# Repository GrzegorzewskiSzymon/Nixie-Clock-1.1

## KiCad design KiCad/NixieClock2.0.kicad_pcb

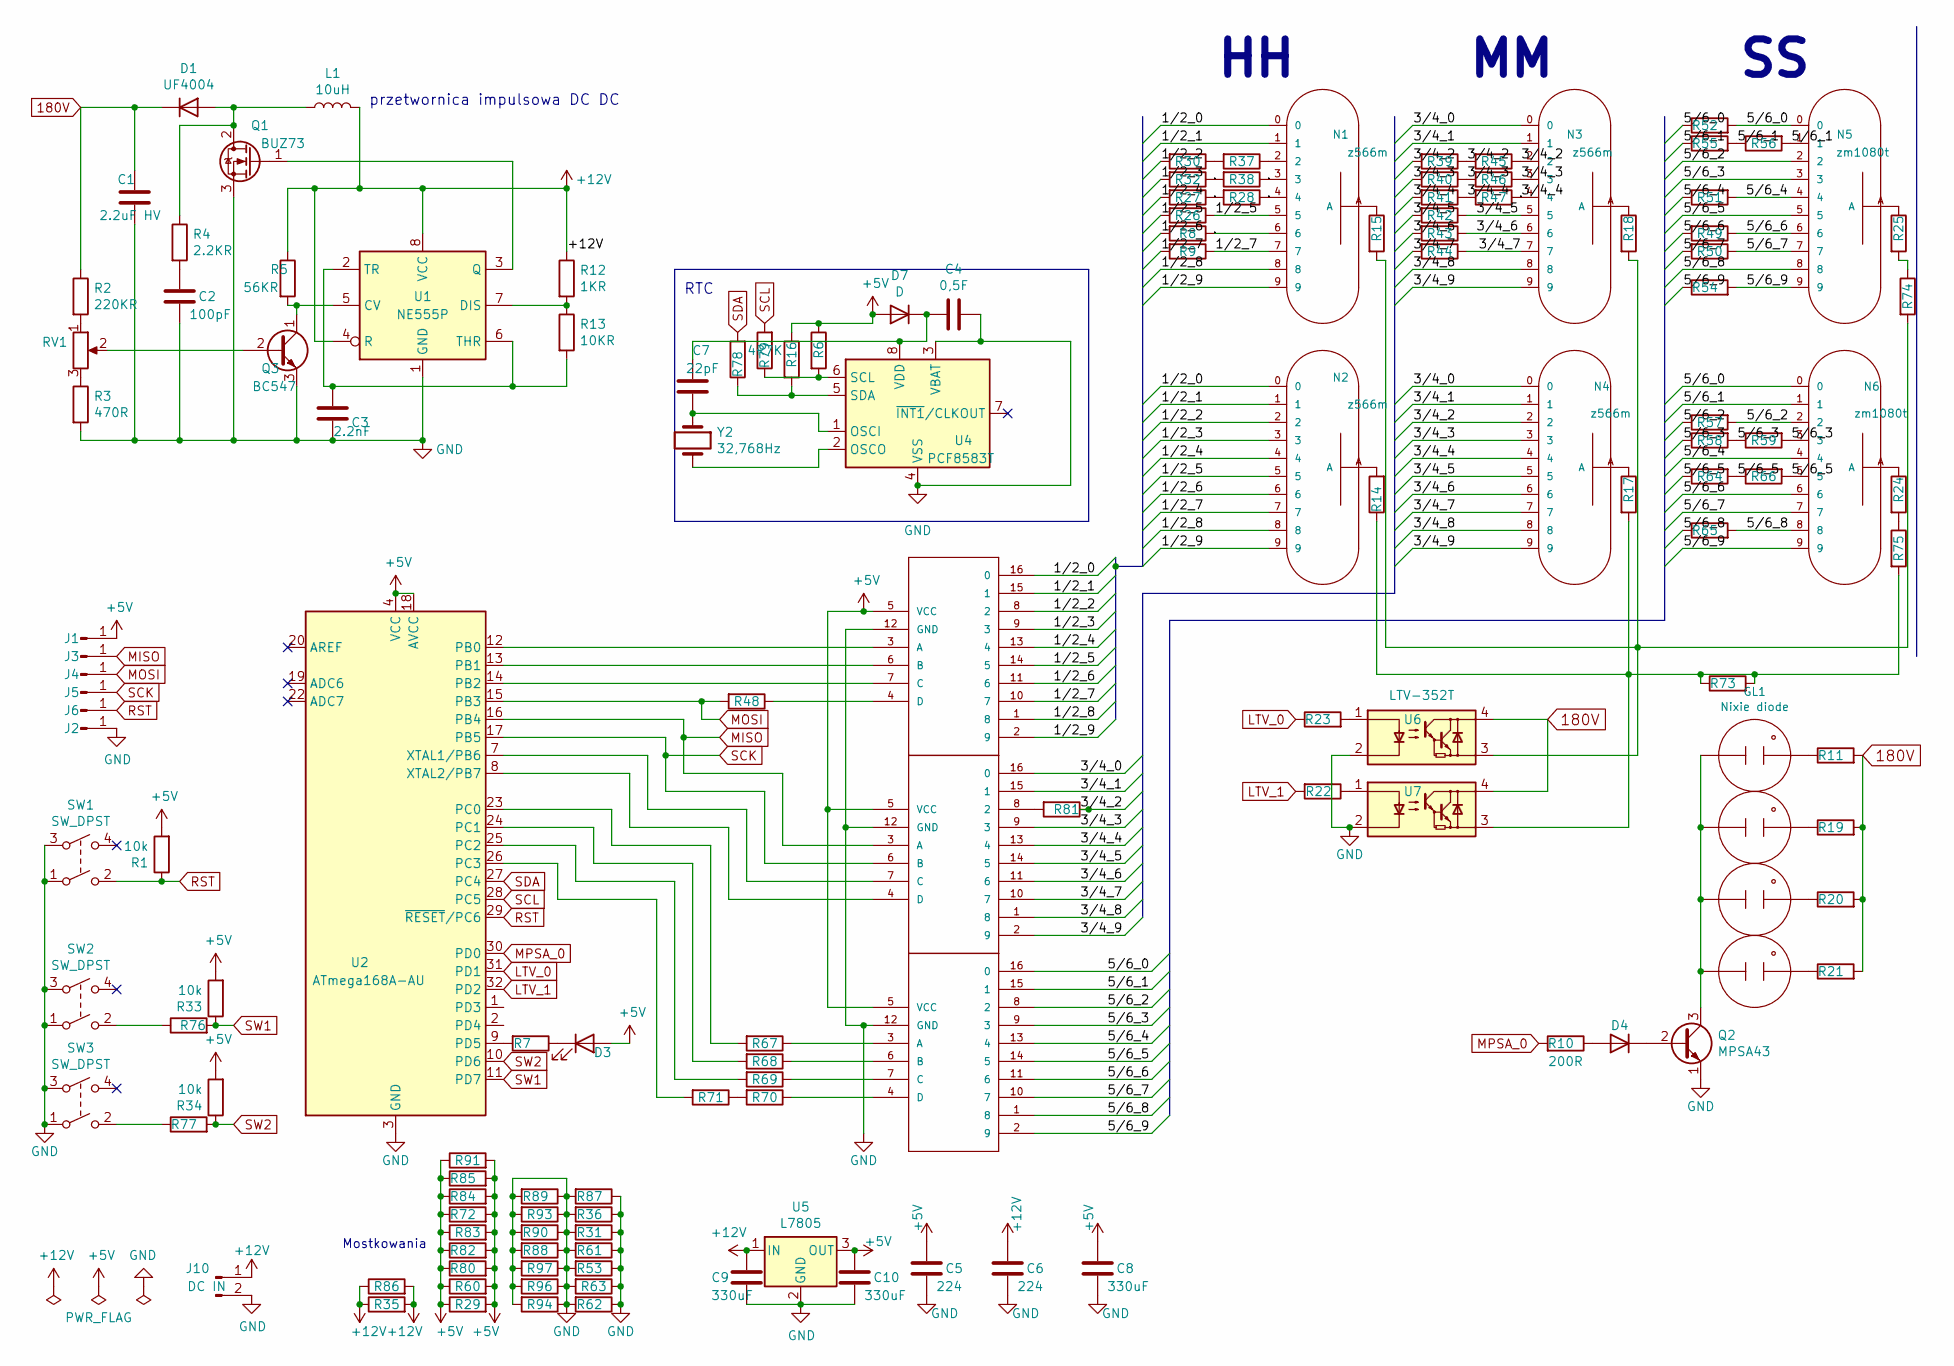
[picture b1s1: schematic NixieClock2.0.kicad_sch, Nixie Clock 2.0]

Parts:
C1: 2.2uF HV; CP_Radial_D8.0mm_P3.80mm
C2: 100pF; C_Disc_D5.0mm_W2.5mm_P5.00mm
C3: 2.2nF; C_Disc_D3.0mm_W2.0mm_P2.50mm
C4: 0,5F; CP_Radial_D6.3mm_P2.50mm
C5, C6: 224; C_Disc_D5.0mm_W2.5mm_P5.00mm
C7: 22pF; C_Disc_D3.0mm_W2.0mm_P2.50mm
C8, C9, C10: 330uF; CP_Radial_D5.0mm_P2.50mm
D1, D4: UF4004; D_DO-35_SOD27_P7.62mm_Horizontal
D3: LED; LED_1206_3216Metric_Pad1.42x1.75mm_HandSolder
D7: D; D_DO-34_SOD68_P7.62mm_Horizontal
GL1, GL2, GL3, GL4: Nixie diode; PinHeader_1x02_P2.54mm_Vertical
J1, J2, J3, J4, J5, J6: Conn_01x01_Male; PinHeader_1x01_P2.54mm_Vertical
J10: DC IN; BarrelJack_CUI_PJ-102AH_Horizontal
L1: 10uH; L_Axial_L6.6mm_D2.7mm_P2.54mm_Vertical_Vishay_IM-2
M1, M2, M3: 74141SOIC16; DIP-16_W7.62mm_LongPads
N1, N2, N3, N4: z566m; z566M
N5, N6: zm1080t; zm1080T
Q1: BUZ73; TO-220-3_Vertical
Q2: MPSA43; TO-92_Inline
Q3: BC547; TO-92_Inline
R1, R33, R34: 10k; R_1206_3216Metric_Pad1.30x1.75mm_HandSolder
R2: 220KR; R_1206_3216Metric_Pad1.30x1.75mm_HandSolder
R3: 470R; R_Axial_DIN0207_L6.3mm_D2.5mm_P7.62mm_Horizontal
R4: 2.2KR; R_1206_3216Metric_Pad1.30x1.75mm_HandSolder
R5: 56KR; R_1206_3216Metric_Pad1.30x1.75mm_HandSolder
R6, R16: 4R7K; R_1206_3216Metric_Pad1.30x1.75mm_HandSolder
R7: 340R; R_Axial_DIN0207_L6.3mm_D2.5mm_P7.62mm_Horizontal
R8, R9, R26, R27, R28, R29, R30, R32, R35, R37, R38, R39, R40, R41, R42, R43, R44, R45, R46, R47, R48, R49, R50, R51, R56, R57, R58, R59, R60, R63, R64, R66, R67, R68, R69, R70, R71, R74, R75, R83, R86, R91, R93, R94, R96, R97: 0R; R_1206_3216Metric_Pad1.30x1.75mm_HandSolder
R10: 200R; R_1206_3216Metric_Pad1.30x1.75mm_HandSolder
R11, R19, R20, R21: 470KR; R_1206_3216Metric_Pad1.30x1.75mm_HandSolder
R12: 1KR; R_1206_3216Metric_Pad1.30x1.75mm_HandSolder
R13: 10KR; R_1206_3216Metric_Pad1.30x1.75mm_HandSolder
R14, R15, R17, R18: 47KR; R_Axial_DIN0207_L6.3mm_D2.5mm_P7.62mm_Horizontal
R22, R23: 340R; R_1206_3216Metric_Pad1.30x1.75mm_HandSolder
R24, R25: 56KR; R_Axial_DIN0207_L6.3mm_D2.5mm_P7.62mm_Horizontal
R31, R36, R52, R53, R54, R55, R61, R62, R65, R72, R73, R76, R77, R78, R79, R80, R81, R82, R84, R85, R87, R88, R89, R90: 0R; R_Axial_DIN0207_L6.3mm_D2.5mm_P7.62mm_Horizontal
RV1: R_POT 1K; Potentiometer_ACP_CA9-H2,5_Horizontal
SW1: SW_DPST; SW_PUSH_6mm_H4.3mm
SW2, SW3: SW_DPST; SW_PUSH-12mm
U1: NE555P; DIP-8_W7.62mm
U2: ATmega168A-AU; TQFP-32_7x7mm_P0.8mm
U4: PCF8583T; SOIC-8_7.5x5.85mm_P1.27mm
U5: L7805; DPAK-3
U6, U7: LTV-352T; SO-4_4.4x3.6mm_P2.54mm
Y2: 32,768Hz; Crystal_DS15_D1.5mm_L5.0mm_Vertical

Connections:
180V: C1.1, D1.1 (K), R2.1, R11.2, R19.2, R20.2, R21.2, U6.4, U7.4
+5V: C5.1, C8.1, C10.1, D3.2 (A), D7.2 (A), J1.1, M1.5 (VCC), M2.5 (VCC), M3.5 (VCC), R1.2, R6.1, R16.1, R29.1, R29.2, R33.2, R34.2, R60.1, R60.2, R72.1, R72.2, R80.1, R80.2, R82.1, R82.2, R83.1, R83.2, R84.1, R84.2, R85.1, R85.2, R91.1, R91.2, U2.4 (VCC), U2.6 (VCC), U2.18 (AVCC), U5.3 (OUT)
+12V: C6.1, C9.1, J10.1, L1.2, R5.1, R12.1, R35.1, R35.2, R86.1, R86.2, U1.4 (R), U1.8 (VCC), U5.1 (IN)
/1/2_0: M1.16 (0), N1.0, N2.0
/1/2_1: M1.15 (1), N1.1, N2.1
/1/2_2: M1.8 (2), N2.2, R30.2
/1/2_3: M1.9 (3), N1.3, N2.3, R32.1, R32.2, R38.1, R38.2
/1/2_4: M1.13 (4), N1.4, N2.4, R27.1, R27.2, R28.1, R28.2
/1/2_5: M1.14 (5), N1.5, N2.5, R26.1, R26.2
/1/2_6: M1.11 (6), N1.6, N2.6, R8.1, R8.2
/1/2_7: M1.10 (7), N1.7, N2.7, R9.1, R9.2
/1/2_8: M1.1 (8), N1.8, N2.8
/1/2_9: M1.2 (9), N1.9, N2.9
/3/4_0: M2.16 (0), N3.0, N4.0
/3/4_1: M2.15 (1), N3.1, N4.1
/3/4_2: N3.2, N4.2, R39.1, R39.2, R45.1, R45.2, R81.1
/3/4_3: M2.9 (3), N3.3, N4.3, R40.1, R40.2, R46.1, R46.2
/3/4_4: M2.13 (4), N3.4, N4.4, R41.1, R41.2, R47.1, R47.2
/3/4_5: M2.14 (5), N3.5, N4.5, R42.1, R42.2
/3/4_6: M2.11 (6), N3.6, N4.6, R43.1, R43.2
/3/4_7: M2.10 (7), N3.7, N4.7, R44.1, R44.2
/3/4_8: M2.1 (8), N3.8, N4.8
/3/4_9: M2.2 (9), N3.9, N4.9
/5/6_0: M3.16 (0), N5.0, N6.0, R52.1, R52.2
/5/6_1: M3.15 (1), N5.1, N6.1, R55.1, R55.2, R56.1, R56.2
/5/6_2: M3.8 (2), N5.2, N6.2, R57.1, R57.2
/5/6_3: M3.9 (3), N5.3, N6.3, R58.1, R58.2, R59.1, R59.2
/5/6_4: M3.13 (4), N5.4, N6.4, R51.1, R51.2
/5/6_5: M3.14 (5), N5.5, N6.5, R64.1, R64.2, R66.1, R66.2
/5/6_6: M3.11 (6), N5.6, N6.6, R49.1, R49.2
/5/6_7: M3.10 (7), N5.7, N6.7, R50.1, R50.2
/5/6_8: M3.1 (8), N5.8, N6.8, R65.1, R65.2
/5/6_9: M3.2 (9), N5.9, N6.9, R54.1, R54.2
GND: C1.2, C2.2, C3.2, C4.2, C5.2, C6.2, C8.2, C9.2, C10.2, J2.1, J10.2, M1.12 (GND), M2.12 (GND), M3.12 (GND), Q1.3 (S), Q2.1 (E), Q3.3 (E), R3.2, R31.1, R31.2, R36.1, R36.2, R53.1, R53.2, R61.1, R61.2, R62.1, R62.2, R63.1, R63.2, R87.1, R87.2, R88.1, R88.2, R89.1, R89.2, R90.1, R90.2, R93.1, R93.2, R94.1, R94.2, R96.1, R96.2, R97.1, R97.2, SW1.1, SW1.3, SW2.1, SW2.3, SW3.1, SW3.3, U1.1 (GND), U2.3 (GND), U2.5 (GND), U2.21 (GND), U4.3 (VBAT), U4.4 (VSS), U5.2 (GND), U6.2, U7.2
LTV_0: R23.1, U2.31 (PD1)
LTV_1: R22.2, U2.32 (PD2)
MISO: J3.1, M2.3 (A), U2.16 (PB4)
MOSI: J4.1, R48.2, U2.15 (PB3)
MPSA_0: R10.2, U2.30 (PD0)
unnamed: C2.1, R4.2
unnamed: C3.1, R13.2, U1.2 (TR), U1.6 (THR)
unnamed: C4.1, C7.2, D7.1 (K), U4.8 (VDD)
unnamed: C7.1, U4.1 (OSCI), Y2.1
unnamed: D1.2 (A), L1.1, Q1.2 (D), R4.1
unnamed: D3.1 (K), R7.1
unnamed: D4.1 (K), Q2.2 (B)
unnamed: D4.2 (A), R10.1
unnamed: GL1.1 (A), GL2.1 (A), GL3.1 (A), GL4.1 (A), Q2.3 (C)
unnamed: GL1.2 (A1), R11.1
unnamed: GL2.2 (A1), R19.1
unnamed: GL3.2 (A1), R20.1
unnamed: GL4.2 (A1), R21.1
unnamed: M1.3 (A), U2.12 (PB0)
unnamed: M1.4 (D), R48.1
unnamed: M1.6 (B), U2.13 (PB1)
unnamed: M1.7 (C), U2.14 (PB2)
unnamed: M2.4 (D), U2.8 (XTAL2/PB7)
unnamed: M2.7 (C), U2.7 (XTAL1/PB6)
unnamed: M2.8 (2), R81.2
unnamed: M3.3 (A), R67.1
unnamed: M3.4 (D), R70.1
unnamed: M3.6 (B), R68.1
unnamed: M3.7 (C), R69.1
unnamed: N1.2, R37.1
unnamed: N1.A, R15.1
unnamed: N2.A, R14.2
unnamed: N3.A, R18.1
unnamed: N4.A, R17.1
unnamed: N5.A, R25.1
unnamed: N6.A, R24.1
unnamed: Q1.1 (G), U1.3 (Q)
unnamed: Q3.1 (C), R5.2, U1.5 (CV)
unnamed: Q3.2 (B), RV1.2
unnamed: R2.2, RV1.1
unnamed: R3.1, RV1.3
unnamed: R6.2, R79.1, U4.6 (SCL)
unnamed: R7.2, U2.9 (PD5)
unnamed: R12.2, R13.1, U1.7 (DIS)
unnamed: R14.1, R17.2, R73.1, R73.2, R75.2, U7.3
unnamed: R15.2, R18.2, R74.2, U6.3
unnamed: R16.2, R78.1, U4.5 (SDA)
unnamed: R22.1, U7.1
unnamed: R23.2, U6.1
unnamed: R24.2, R75.1
unnamed: R25.2, R74.1
unnamed: R30.1, R37.2
unnamed: R67.2, U2.23 (PC0)
unnamed: R68.2, U2.24 (PC1)
unnamed: R69.2, U2.25 (PC2)
unnamed: R70.2, R71.1
unnamed: R71.2, U2.26 (PC3)
unnamed: R76.1, SW2.2
unnamed: R77.1, SW3.2
unnamed: U4.2 (OSCO), Y2.2
RST: J6.1, R1.1, SW1.2, U2.29 (~RESET/PC6)
SCK: J5.1, M2.6 (B), U2.17 (PB5)
SCL: R79.2, U2.28 (PC5)
SDA: R78.2, U2.27 (PC4)
SW1: R33.1, R76.2, U2.11 (PD7)
SW2: R34.1, R77.2, U2.10 (PD6)

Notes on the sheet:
RTC
Mostkowania
przetwornica impulsowa DC DC

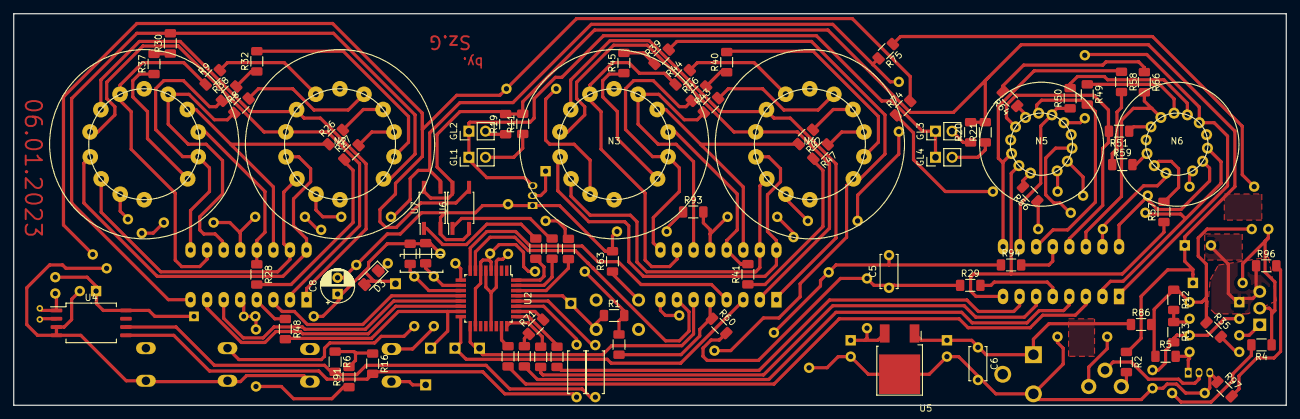
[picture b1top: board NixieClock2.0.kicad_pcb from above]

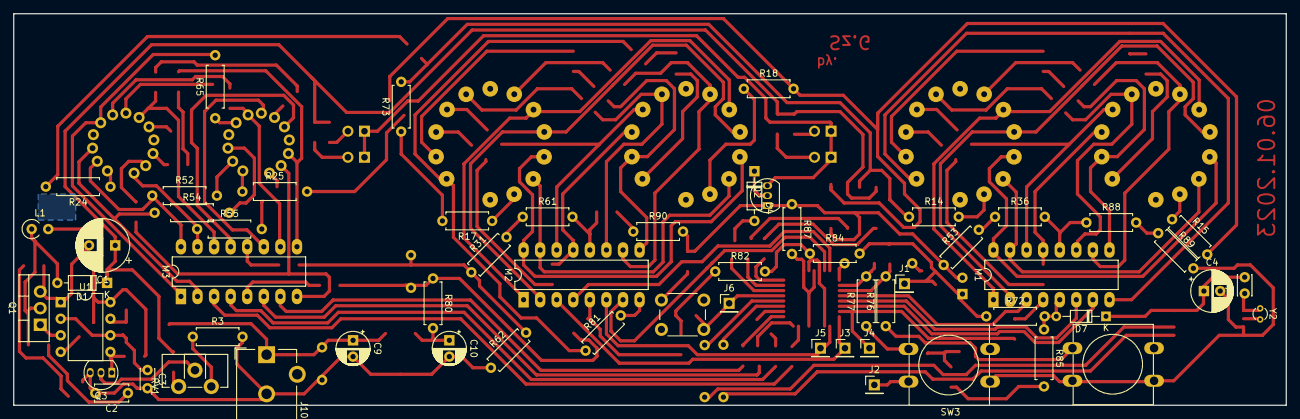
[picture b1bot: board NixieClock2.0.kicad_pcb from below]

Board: 2 copper layers, 195.0 x 60.0 mm, 144 parts (59 on the bottom side), 100 nets.

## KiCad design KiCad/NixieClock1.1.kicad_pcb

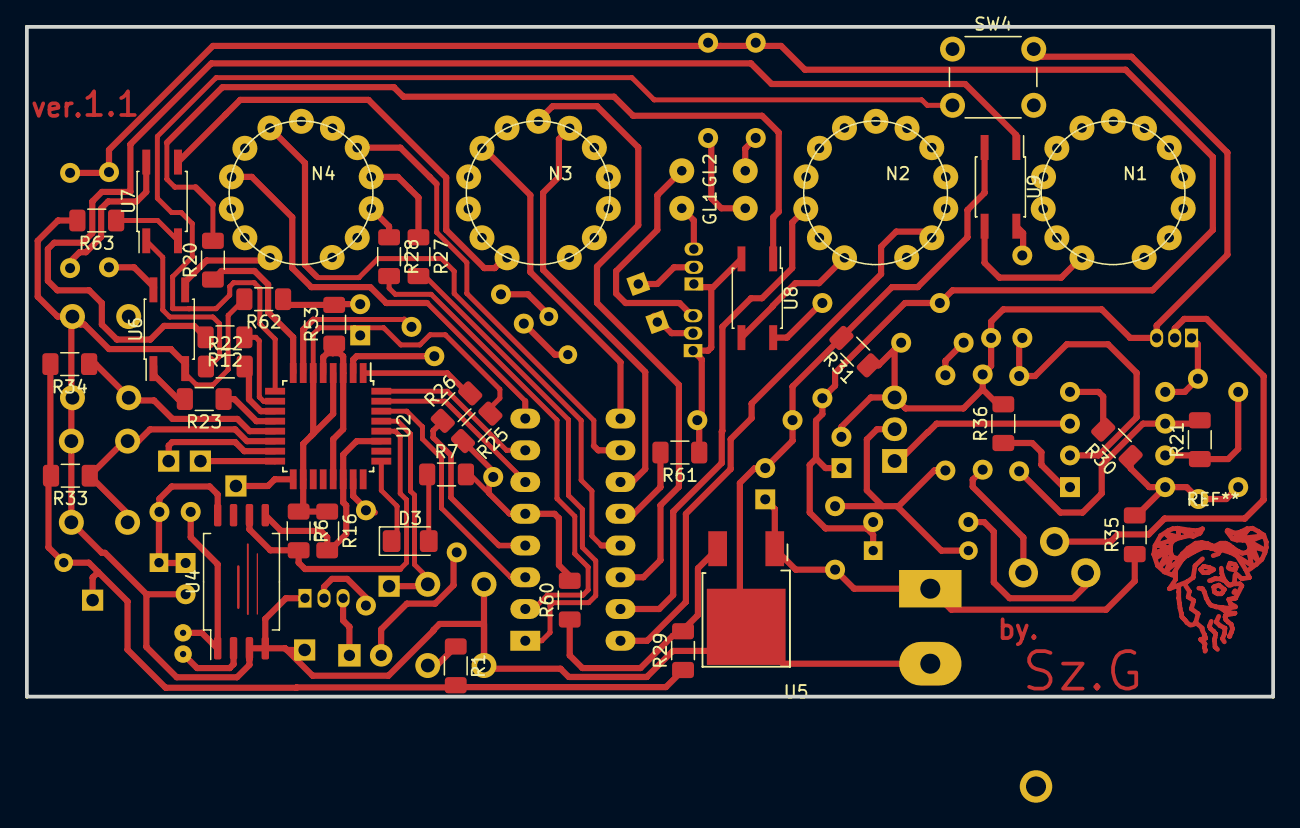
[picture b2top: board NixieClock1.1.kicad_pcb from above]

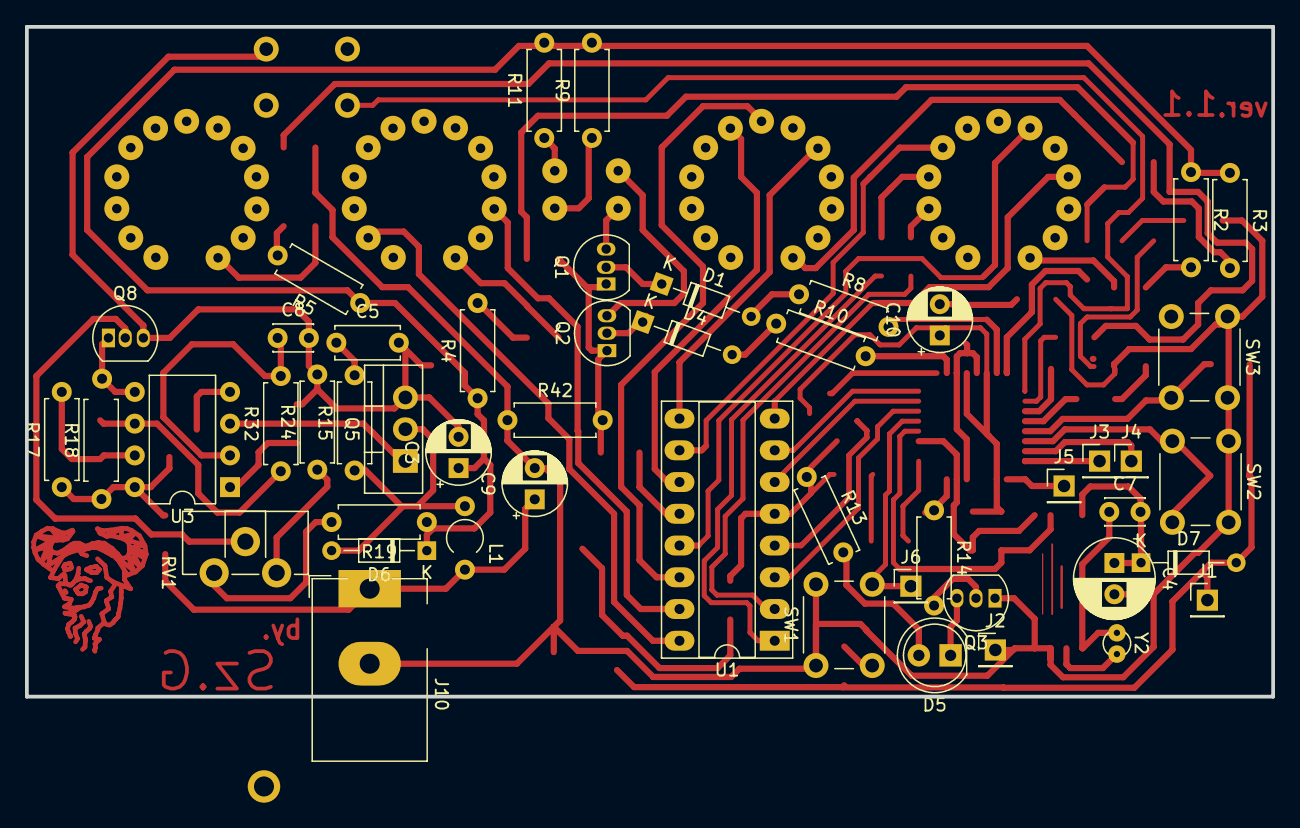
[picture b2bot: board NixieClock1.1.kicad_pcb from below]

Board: 2 copper layers, 99.7 x 53.6 mm, 89 parts (49 on the bottom side), 75 nets.

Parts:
C3: 2.2uF HV; CP_Radial_D5.0mm_P2.50mm
C4: 0,5F; CP_Radial_D6.3mm_P2.50mm
C5: 100pF; C_Disc_D5.0mm_W2.5mm_P5.00mm
C7: 22pF; C_Disc_D3.0mm_W2.0mm_P2.50mm
C8: 2.2nF; C_Disc_D3.0mm_W2.0mm_P2.50mm
C9, C10: 330uF; CP_Radial_D5.0mm_P2.50mm
D1, D4, D6: UF4004; D_DO-34_SOD68_P7.62mm_Horizontal
D3: LED; LED_1206_3216Metric_Pad1.42x1.75mm_HandSolder
D5: LED; LED_D5.0mm
D7: D; D_DO-34_SOD68_P7.62mm_Horizontal
GL1, GL2: Nixie diode
J1, J2, J3, J4, J5, J6: Conn_01x01_Male; PinHeader_1x01_P2.54mm_Vertical
J10: DC IN; BarrelJack_CUI_PJ-102AH_Horizontal
L1: 100uH; L_Axial_L6.6mm_D2.7mm_P2.54mm_Vertical_Vishay_IM-2
N1, N2, N3, N4: 6844AD-SUB; LC-531
Q1, Q2: MPSA43; TO-92_Inline
Q3: S8550; TO-92_Inline
Q5: BUZ73; TO-220-3_Vertical
Q8: BC547; TO-92_Inline
R1, R33, R34: 10k; R_1206_3216Metric_Pad1.30x1.75mm_HandSolder
R2, R3, R4, R5, R9, R11: 47KR; R_Axial_DIN0207_L6.3mm_D2.5mm_P7.62mm_Horizontal
R6, R16: 4R7K; R_1206_3216Metric_Pad1.30x1.75mm_HandSolder
R7: 330R; R_1206_3216Metric_Pad1.30x1.75mm_HandSolder
R8, R10: 200R; R_Axial_DIN0207_L6.3mm_D2.5mm_P7.62mm_Horizontal
R12, R20, R22, R23, R27, R28: 340R; R_1206_3216Metric_Pad1.30x1.75mm_HandSolder
R13: 47R; R_Axial_DIN0207_L6.3mm_D2.5mm_P7.62mm_Horizontal
R14: 4R7K; R_Axial_DIN0207_L6.3mm_D2.5mm_P7.62mm_Horizontal
R15: 2.2KR; R_Axial_DIN0207_L6.3mm_D2.5mm_P7.62mm_Horizontal
R17: 1KR; R_Axial_DIN0207_L6.3mm_D2.5mm_P7.62mm_Horizontal
R18: 56KR; R_Axial_DIN0207_L6.3mm_D2.5mm_P7.62mm_Horizontal
R19: 220KR; R_Axial_DIN0207_L6.3mm_D2.5mm_P7.62mm_Horizontal
R21: 10KR; R_1206_3216Metric_Pad1.30x1.75mm_HandSolder
R24: 470R; R_Axial_DIN0207_L6.3mm_D2.5mm_P7.62mm_Horizontal
R25, R26, R29, R30, R31, R35, R36, R53, R60, R61, R62, R63: 0R; R_1206_3216Metric_Pad1.30x1.75mm_HandSolder
R32, R42: 0R; R_Axial_DIN0207_L6.3mm_D2.5mm_P7.62mm_Horizontal
RV1: R_POT 1K; Potentiometer_ACP_CA9-H2,5_Horizontal
SW1, SW2, SW3, SW4: SW_DPST; SW_PUSH_6mm_H4.3mm
U1: 74141; DIP-16_W7.62mm_Socket_LongPads
U2: ATmega168A-AU; TQFP-32_7x7mm_P0.8mm
U3: NE555P; DIP-8_W7.62mm
U4: PCF8583T; SOIC-8_7.5x5.85mm_P1.27mm
U5: L7805; DPAK-3
U6, U7, U8, U9: LTV-352T; SO-4_4.4x3.6mm_P2.54mm
Y2: 32,768Hz; Crystal_DS15_D1.5mm_L5.0mm_Vertical

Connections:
180V: C3.1, D6.1, R2.1, R3.1, R4.1, R5.1, R9.2, R11.2, R19.1
+5V: C10.1, D7.2, J1.1, R1.2, R6.1, R7.2, R13.1, R16.1, R25.1, R25.2, R29.1, R29.2, R33.2, R34.2, R60.1, R60.2, U1.5, U2.4, U2.6, U2.18, U5.3
+12V: C9.1, J10.1, L1.2, R17.1, R18.1, R30.1, R30.2, R35.1, R35.2, U3.4, U3.8, U5.1
/0: N2.0, U1.16
/1: N2.1, U1.15
/2: N4.2, U1.8
/3: N3.3, U1.9
/4: N4.4, U1.13
/5: N3.5, U1.14
/6: N3.6, U1.11
/7: N4.7, U1.10
/8: R27.2, U1.1
/9: R28.2, U1.2
GND: C3.2, C4.2, C5.2, C8.2, C9.2, C10.2, J2.1, J10.2, Q1.1, Q2.1, Q3.1, Q5.3, Q8.3, R24.2, R31.1, R31.2, R36.1, R36.2, R42.1, R42.2, R53.1, R53.2, R61.1, R61.2, R62.1, R62.2, R63.1, R63.2, SW1.1, SW2.1, SW3.1, SW4.1, U1.12, U2.3, U2.5, U2.21, U3.1, U4.3, U4.4, U5.2, U6.2, U7.2, U8.2, U9.2
IR: R14.1, U2.23
MISO: J3.1, U2.16
MOSI: J4.1, U2.15
unnamed: C4.1, C7.2, D7.1, U4.8
unnamed: C5.1, R15.2
unnamed: C7.1, U4.1, Y2.1
unnamed: C8.1, R32.2, U3.2
unnamed: D1.1, Q1.2
unnamed: D1.2, R8.1
unnamed: D3.1, U2.25
unnamed: D3.2, R7.1
unnamed: D4.1, Q2.2
unnamed: D4.2, R10.1
unnamed: D5.1, Q3.3
unnamed: D5.2, R13.2
unnamed: D6.2, L1.1, Q5.2, R15.1
unnamed: GL1.1, Q1.3
unnamed: GL1.2, R9.1
unnamed: GL2.1, Q2.3
unnamed: GL2.2, R11.1
unnamed: N1.A, U9.3
unnamed: N2.A, U8.3
unnamed: N3.A, U7.3
unnamed: N4.8, R27.1
unnamed: N4.9, R28.1
unnamed: N4.A, U6.3
unnamed: Q3.2, R14.2
unnamed: Q5.1, U3.3
unnamed: Q8.1, R18.2, U3.5
unnamed: Q8.2, RV1.2
unnamed: R2.2, U6.4
unnamed: R3.2, U7.4
unnamed: R4.2, U8.4
unnamed: R5.2, U9.4
unnamed: R8.2, U2.7
unnamed: R10.2, U2.2
unnamed: R12.1, U2.10
unnamed: R12.2, U9.1
unnamed: R17.2, R21.1, U3.7
unnamed: R19.2, RV1.1
unnamed: R20.1, U2.8
unnamed: R20.2, U8.1
unnamed: R21.2, R32.1, U3.6
unnamed: R22.1, U7.1
unnamed: R22.2, U2.11
unnamed: R23.1, U2.12
unnamed: R23.2, U6.1
unnamed: R24.1, RV1.3
unnamed: R26.1, U1.4
unnamed: R26.2, U2.1
unnamed: U1.3, U2.30
unnamed: U1.6, U2.31
unnamed: U1.7, U2.32
unnamed: U4.2, Y2.2
RST: J6.1, R1.1, SW1.2, U2.29
SCK: J5.1, U2.17
SCL: R6.2, U2.28, U4.6
SDA: R16.2, U2.27, U4.5
SW1: R33.1, SW2.2, U2.14
SW2: R34.1, SW3.2, U2.13
SW3: SW4.2, U2.9

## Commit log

2022-06-17 add .gitignore
2022-06-17 add "Timer0_Init()" function to start counting milliseconds, needed for future non blocking implementations
    add "Led_Init()" and "BlinkLed()"
    add preprocessor implementations in "utils.h"
2022-06-18 add non blocking functions to count number of presses on buttons, along with fast counting after pressing button for over 2sec (can be easily change in utils.h)
2022-06-22 add macros -to control transoptors which multiplexes anodes -to control SN74141 to control which digit is lighted
2022-06-27 add function DisplayTime(h, m) to show hours and minutes on nixie tubes
2022-06-27 add preprocessor directives to turn on and off nixie tubes
2022-06-27 add hardware i2c implementations for future communication with RTC
2022-06-28 add functions -RtcInit() allow user to change time in RTC -RtcReadData() to pull data from RTC
2022-06-28 using previously written funcions for: -basic initialization of periferies -simple pulling data from rtc with displaying it
2022-07-03 add simple directives to control nixie diodes add NixieDiodesInit() to set pins as outputs
2022-07-03 add one millisecond of turned off tubes between switching between them, because optocoupler LTV-352T switch off characteristics coused ghost digits
2022-07-03 add simple blinking of nixie diodes every 6sec
2022-07-09 add IR library to communicate in this particular project with my lighting room system mainly to try wake me up
2022-07-12 add states of clock with different actions as IDLE then after setting designated hour, clock changes to SUSTAIN and wants to press a button within each 15 minutes, if not, goes to ALARMED mode and se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
2022-09-02 add schematic and one layer pcb layout
2022-09-02 fixed wrong buffer indexing, witch cause bugs when user goes over 24 hours
2022-09-02 clear code
2022-09-15 change pins attatchments (new schematic and pcb layout)
2022-09-15 change whole DisplayTime(...) function (caused by new schematic and pcb layout)
2022-09-15 new function for only two buttons, to insert time to RTC
2022-09-15 combine new functions
2022-09-15 add schematics and one layer pcb layout
2022-12-08 add additional * seconds to the time to send to RTC, * the amount of time which the function for setting time will take from last press of a button
2022-12-08 turn off all tubes for one ms after every switch between displaying tens and units to cancel ghost numbers in tubes
2022-12-08 fix bug: inserting ms as sec to RTC in initialization
2022-12-09 add new mode of slow displaying and use it when it's time to "repair" balance in nixie tubes
2022-12-09 change the look of the mode for slow displaying
